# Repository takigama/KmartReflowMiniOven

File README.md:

# KMART REFLOW MINI OVEN

its only just started and the code is ugly as sin.

The goal is to produce a codebase that might be useful for any reflow oven where:
 - heat control is done via SSR (100hz cycle)
 - Temperature via a thermistor (similar to 3d printer)
 - Lilygo t-display controller (with a daughter board), but this might be changed later for something more "modular"

## But Why?

Yes, I know theres tonnes of toaster oven reflow ovens around (I even have one!), but this one is half the size
and half the price and felt like a fun project...

## General Thoughts...

Much of the code will be similar to 3d printers because alot of the features are similar, plus to make it module it
sort of makes sense to use the 3d printer board base as it already has all the modularity for things like tft screens, 
thermistors, etc.

## TODO
 - the web interface (im terrible at making pretty ui's)
 - design the daughter board for the lilygo t-display to 4 temperature sensors and 2 SSR controls

## DONE
 - made a small test board
 - add wifimanager - done

## Hackaday Build log

[Hackaday Page](https://hackaday.io/project/202428-another-mini-reflow-oven)
 
## Pics

And here the oven is in all its glory (prior to a working oven - coke can to show off size)

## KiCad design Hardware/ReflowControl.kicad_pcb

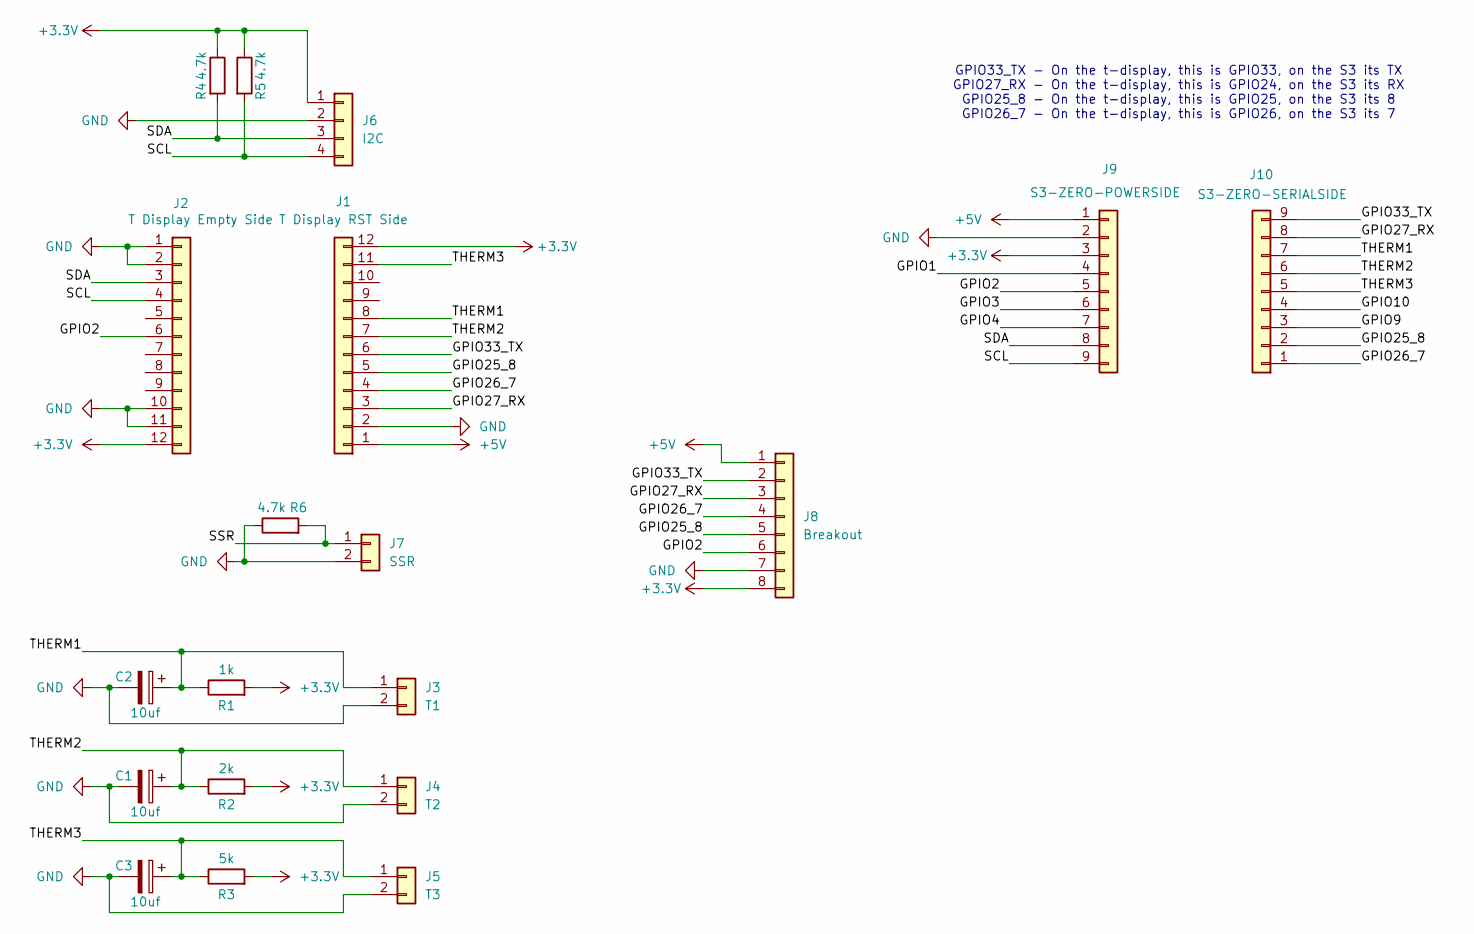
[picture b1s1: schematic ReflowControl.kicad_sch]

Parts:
C1, C2, C3: 10uf; C_1206_3216Metric_Pad1.33x1.80mm_HandSolder
J1: T Display RST Side; PinHeader_1x12_P2.54mm_Vertical
J2: T Display Empty Side; PinHeader_1x12_P2.54mm_Vertical
J3: T1; PinHeader_1x02_P2.54mm_Vertical
J4: T2; PinHeader_1x02_P2.54mm_Vertical
J5: T3; PinHeader_1x02_P2.54mm_Vertical
J6: I2C; PinHeader_1x04_P2.54mm_Vertical
J7: SSR; PinHeader_1x02_P2.54mm_Vertical
J8: Breakout; PinHeader_1x08_P2.54mm_Vertical
J9: S3-ZERO-POWERSIDE; PinHeader_1x09_P2.54mm_Vertical
J10: S3-ZERO-SERIALSIDE; PinHeader_1x09_P2.54mm_Vertical
R1: 1k; R_0805_2012Metric_Pad1.20x1.40mm_HandSolder
R2: 2k; R_0805_2012Metric_Pad1.20x1.40mm_HandSolder
R3: 5k; R_0805_2012Metric_Pad1.20x1.40mm_HandSolder
R4, R5, R6: 4.7k; R_0805_2012Metric_Pad1.20x1.40mm_HandSolder

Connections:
+3.3V: J1.12, J2.12, J6.1, J8.8, J9.3, R1.2, R2.2, R3.2, R4.1, R5.1
+5V: J1.1, J8.1, J9.1
/GPIO1: J9.4
/GPIO2: J2.6, J8.6, J9.5
/GPIO3: J9.6
/GPIO4: J9.7
/GPIO9: J10.3
/GPIO10: J10.4
/GPIO25_8: J1.5, J8.5, J10.2
/GPIO26_7: J1.4, J8.4, J10.1
/GPIO27_RX: J1.3, J8.3, J10.8
/GPIO33_TX: J1.6, J8.2, J10.9
/SCL: J2.4, J6.4, J9.9, R5.2
/SDA: J2.3, J6.3, J9.8, R4.2
/SSR: J7.1, R6.2
/THERM1: C2.1, J1.8, J3.1, J10.7, R1.1
/THERM2: C1.1, J1.7, J4.1, J10.6, R2.1
/THERM3: C3.1, J1.11, J5.1, J10.5, R3.1
GND: C1.2, C2.2, C3.2, J1.2, J2.1, J2.2, J2.10, J2.11, J3.2, J4.2, J5.2, J6.2, J7.2, J8.7, J9.2, R6.1

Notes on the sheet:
GPIO33_TX - On the t-display, this is GPIO33, on the S3 its TX GPIO27_RX - On the t-display, this is GPIO24, on the S3 its RX GPIO25_8 - On the t-display, this is GPIO25, on the S3 its 8 GPIO26_7 - On the t-display, this is GPIO26, on the S3 its 7

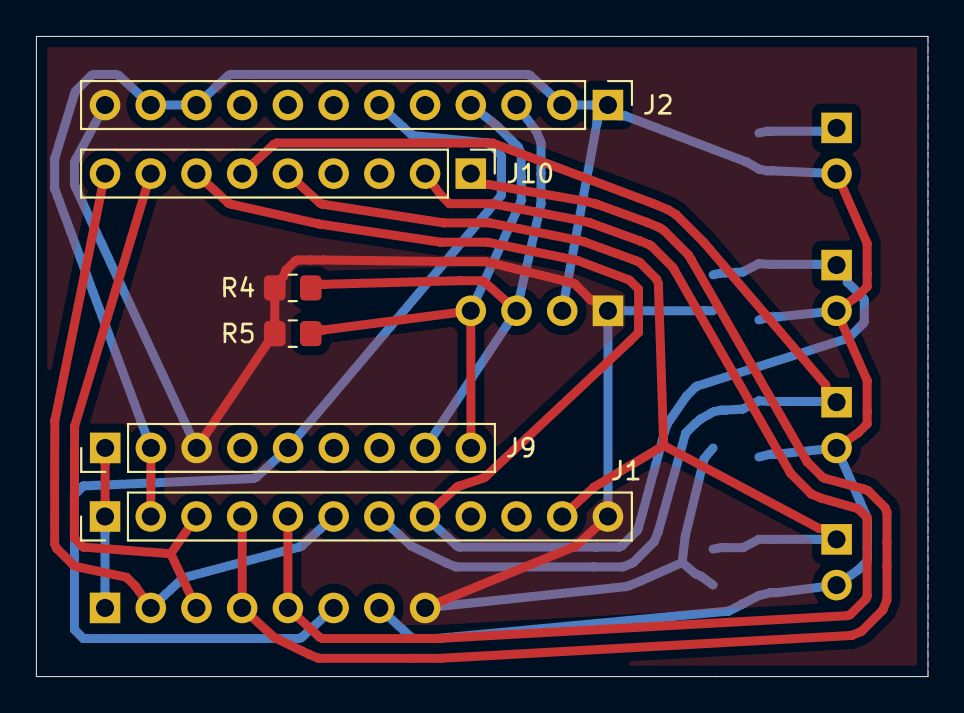
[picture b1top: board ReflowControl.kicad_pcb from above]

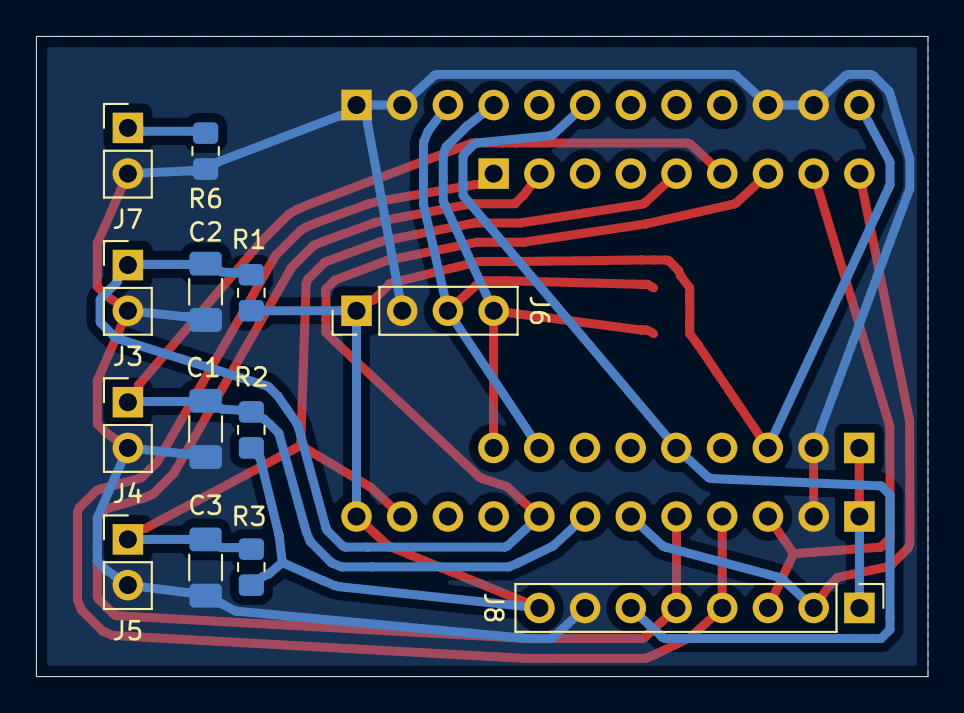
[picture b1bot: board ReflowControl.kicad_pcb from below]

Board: 2 copper layers, 49.5 x 35.6 mm, 19 parts (13 on the bottom side), 14 nets.

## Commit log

2025-02-17 added a readme
2025-02-17 add pic
2025-02-17 update readmie
2025-02-17 i broke compilation
2025-02-18 silly headerfile name
2025-02-18 small test board
2025-02-20 Updated Design cause ADC2 cant be used
2025-02-20 changes to the pin layout
2025-02-20 Hard design update
2025-02-21 add the ntc thermistor library for reading the thermistor
2025-02-21 some testing code
2025-02-22 testing loop
2025-02-22 test loop
2025-02-22 i've added an aggregate temperature class that can deal with multiple thermistors with different ranges and do useful things with the data
2025-02-22 its not getting to 300 seconds, which is weird
2025-02-25 implementing pushing temperature profiles to the device
2025-03-01 oopsie no2 - wrong board pin header orientation and added an s3 board as a secondary pin headout
2025-03-01 first set of alignment data
2025-03-01 quick test of posting json temp profiles
